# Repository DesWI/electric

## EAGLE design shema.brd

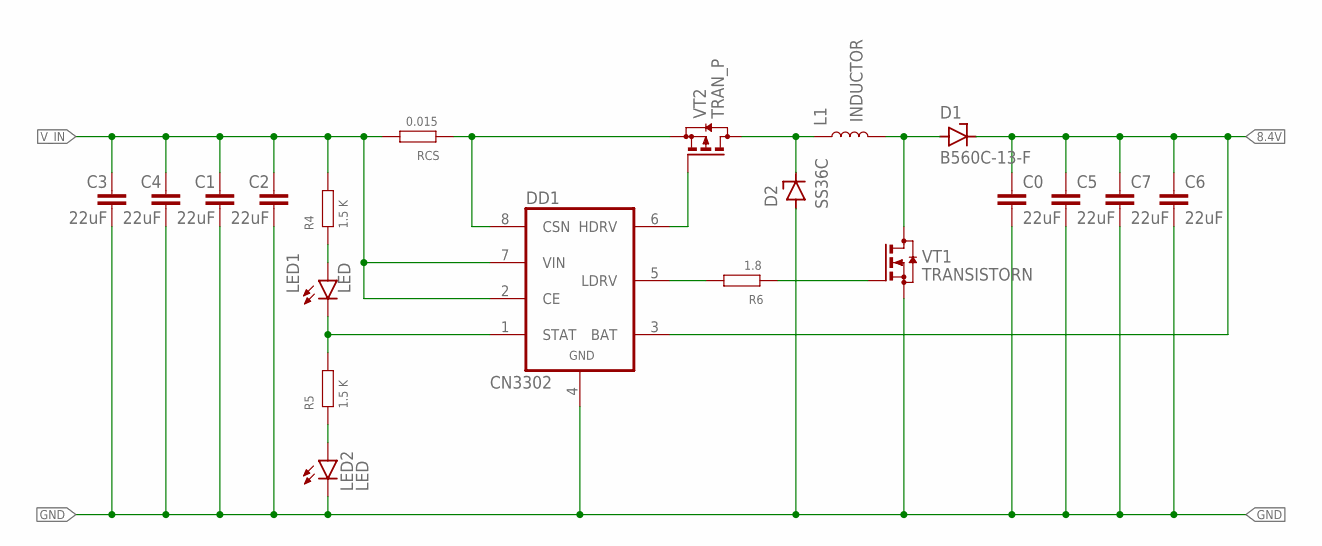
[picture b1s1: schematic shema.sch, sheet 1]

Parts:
C0, C1, C2, C3, C4, C5, C6, C7: 22uF; 1206
D1: B560C-13-F; CB417-15
D2: SS36C; DIOD
DD1: CN3302; SOP-8
L1: INDUCTOR; SMD
LED1, LED2: LED; 1206
R4, R5: 1.5 K; 0603
R6: 1.8; 0603
RCS: 0.015; 2512
VT1: TRANSISTORN; PDFN5*6-8L
VT2: TRAN_P; SOP-8

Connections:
8.4V: C0.P$1 (1), C5.P$1 (1), C6.P$1 (1), C7.P$1 (1), D1.C, DD1.3 (BAT)
GND: C0.P$2 (2), C1.P$2 (2), C2.P$2 (2), C3.P$2 (2), C4.P$2 (2), C5.P$2 (2), C6.P$2 (2), C7.P$2 (2), D2.A, DD1.4 (GND), LED2.C, VT1.P$5 (S), VT1.P$6 (S), VT1.P$7 (S)
unnamed: LED2.A, R5.P$1
unnamed: DD1.8 (CSN), RCS.P$1, VT2.P$1 (S), VT2.P$2 (S), VT2.P$3 (S)
unnamed: D2.C, L1.P$1 (1), VT2.P$5 (D), VT2.P$6 (D), VT2.P$7 (D), VT2.P$8 (D)
unnamed: D1.A, L1.P$2 (2), VT1.P$1 (D), VT1.P$2 (D), VT1.P$3 (D), VT1.P$4 (D), VT1.P$9 (D)
unnamed: DD1.5 (LDRV), R6.P$2
unnamed: R6.P$1, VT1.P$8 (G)
unnamed: DD1.6 (HDRV), VT2.P$4 (G)
unnamed: DD1.1 (STAT), LED1.C, R5.P$2
unnamed: LED1.A, R4.P$1
V_IN: C1.P$1 (1), C2.P$1 (1), C3.P$1 (1), C4.P$1 (1), DD1.2 (CE), DD1.7 (VIN), R4.P$2, RCS.P$2

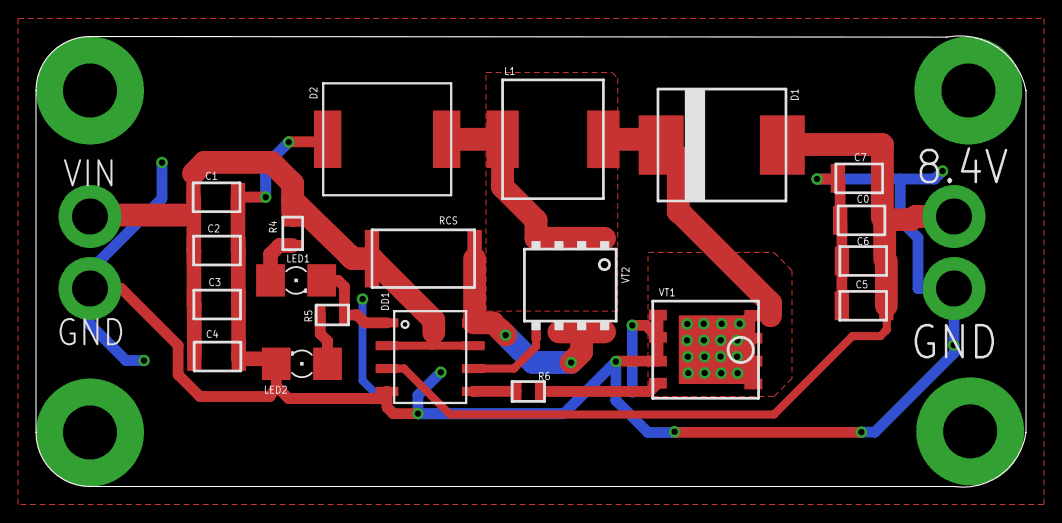
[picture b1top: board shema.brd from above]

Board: 2 copper layers, 55.0 x 25.1 mm, 20 parts (0 on the bottom side), 12 nets.

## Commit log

2023-09-29 оставил комментарий
2023-10-06 добавила библиотеки
2023-10-06 diode fix
2023-10-06 отредактировал библиотеку конденстаторов и резисторов
2023-10-06 файл
2023-10-12 изменила файлы
2023-10-12 добавила файлы
2023-10-12 фиксы
2023-10-12 файлы изменение
2023-10-19 Файлы обновлены
2023-10-19 изменения файлов
2023-10-19 изменение файлов
2023-10-19 файлы изменения
2023-10-19 новые файлы Э '
2023-10-19 новые файлы
2023-10-26 новый файл
2023-10-26 рецензия
2023-10-30 изменение файла
